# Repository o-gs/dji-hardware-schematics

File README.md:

# dji-hardware-schematics
Community made schematics for the DJI drones and devices.

The repository stored KiCad projects with schematocs and PCBs of various parts of DJI hardware.
These projects are community made, and very likely have errors. They come with no warranty.

If you see an error in a schematic, or want to contribute your own - you are free to do it. Your contribution will be verified and accepted into this repository.

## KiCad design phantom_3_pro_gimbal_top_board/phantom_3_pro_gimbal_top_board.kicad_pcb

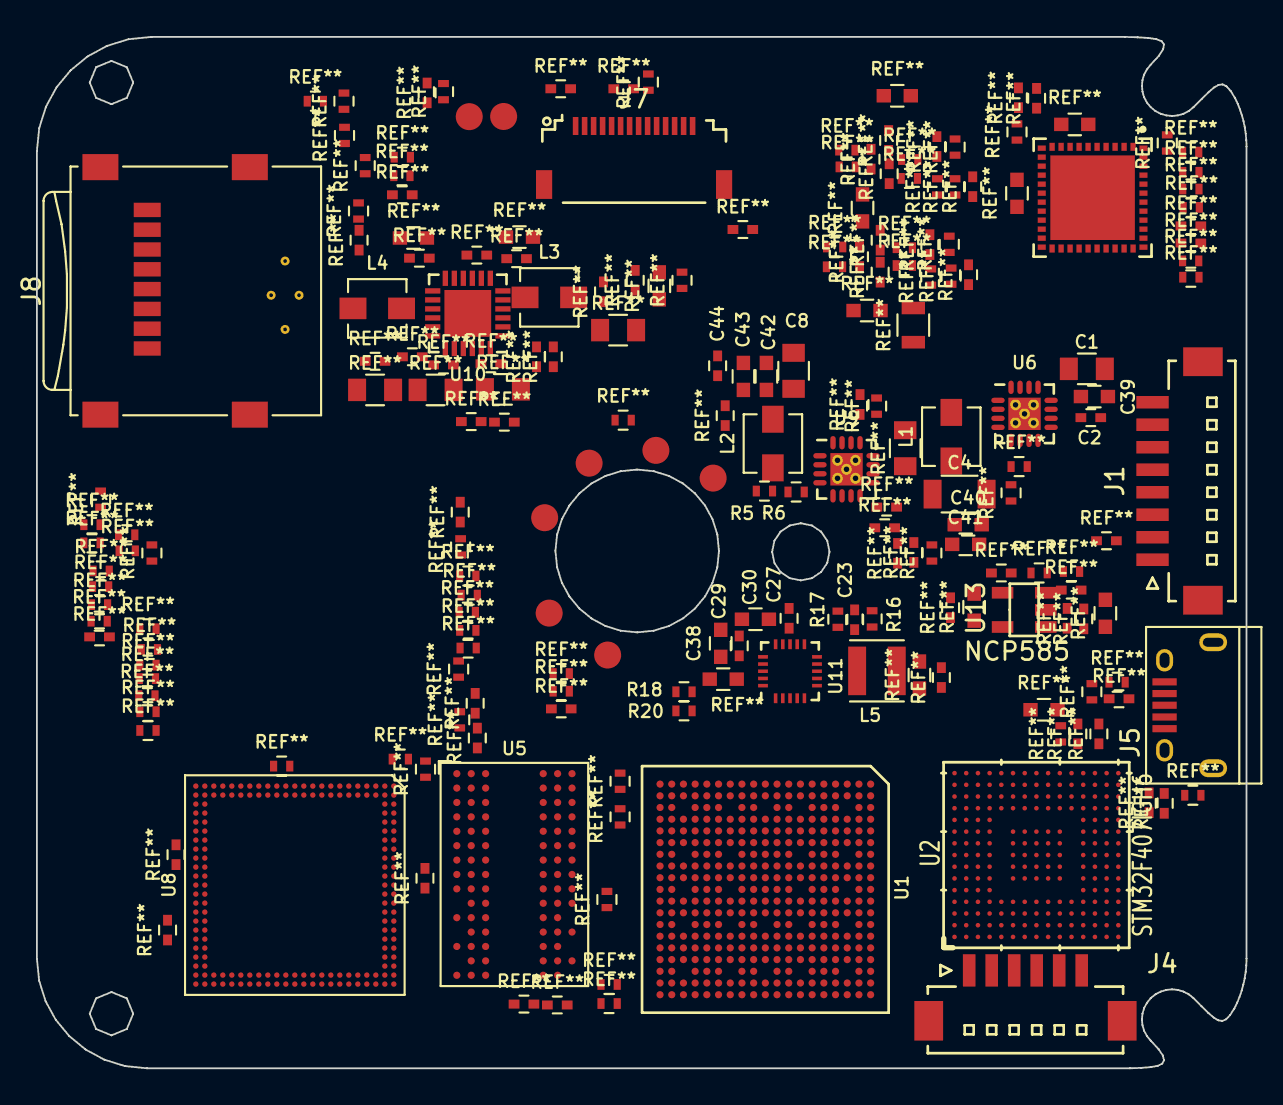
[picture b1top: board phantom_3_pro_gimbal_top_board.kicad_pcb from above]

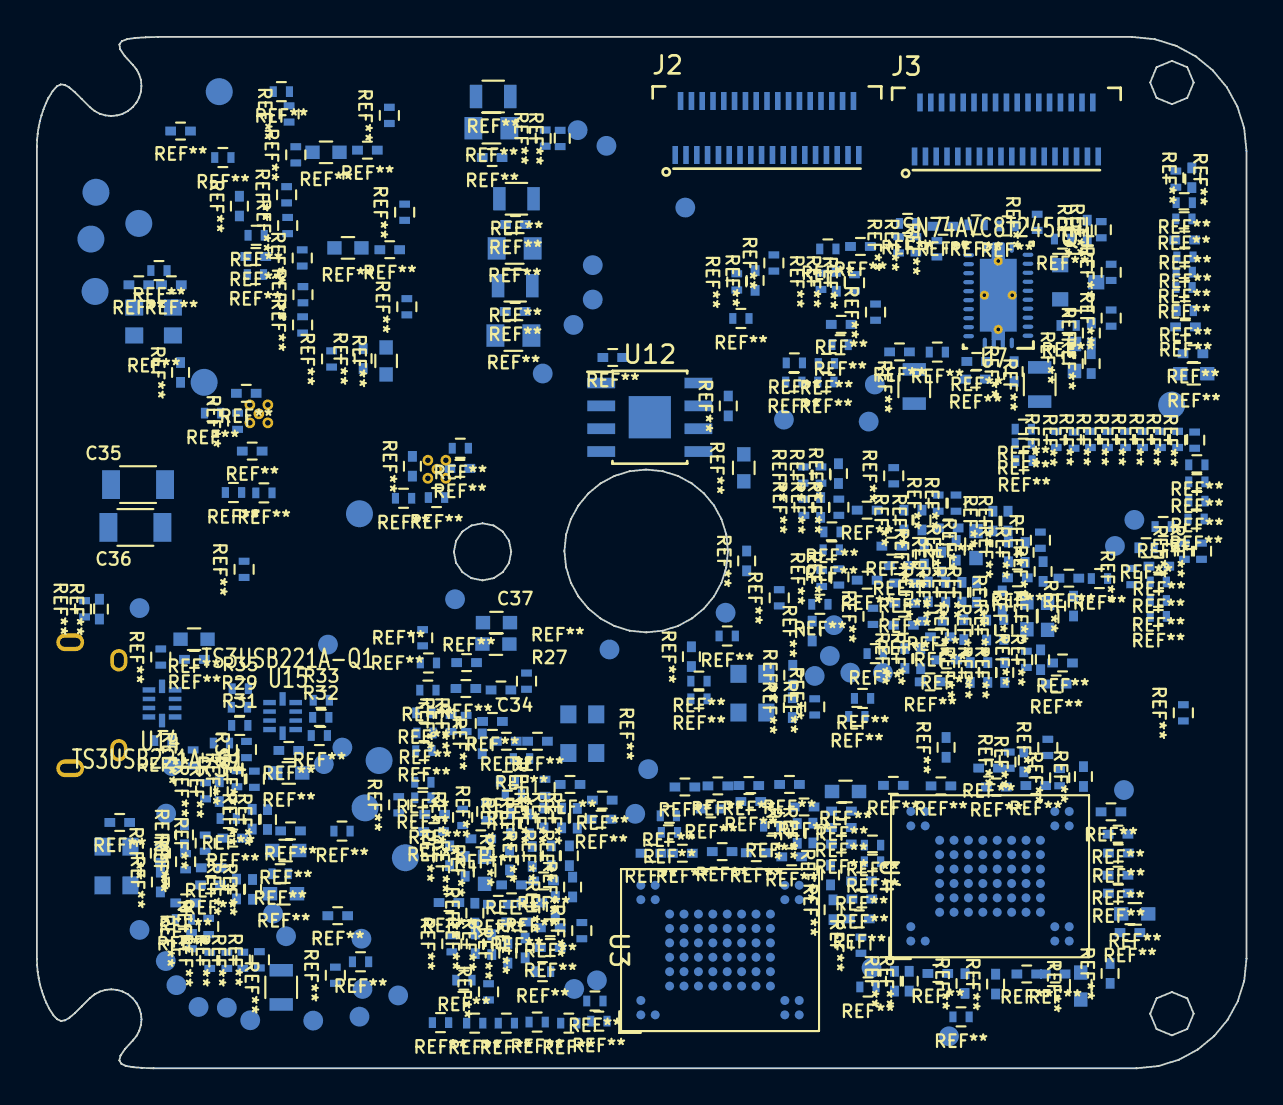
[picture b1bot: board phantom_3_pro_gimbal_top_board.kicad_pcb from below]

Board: 2 copper layers, 67.2 x 57.3 mm, 127 parts (78 on the bottom side), 45 nets, no tracks yet.

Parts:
C1: 10uF?; C_0805
C2: 100nF?; C_0402
C4: 2.2uF?; C_1206
C8: 2.2uF?; C_0805
C23: 22pF; C_0402
C27, C29: 10nF?; C_0402
C30, C37, C38: 2.2uF?; C_0603
C34: 1uF?; C_0402
C35, C36: 22uF?; C_1206
C39, C40, C42: 100nF?; C_0603
C41, C43: 10nF?; C_0603
C44: 100pF?; C_0402
J1: CONN_CENTER; Hirose_DF13C-08P-1.25V_08x1.25mm_Straight
J2: CONN_ARMS2; Flat_Foam_Conn-ZIF-35D-0.6H_35x0.60mm_Angled
J3: CONN_ARMS1; Flat_Foam_Conn-ZIF-35D-0.6H_35x0.60mm_Angled
J4: CONN_OFDM; Hirose_DF13C-06P-1.25V_06x1.25mm_Straight
J5: USB_OTG; USB_Micro-B
J7: CONN_MOTOR; Flat_Foam_Conn-14S-0.5H_14x0.50mm_Angled
J8: Micro_SD_Card; microSD_Card_Receptacle_Wuerth_693072010801
L1, L2, L3, L4: 2.2uH; L_Vishay_IHLP-1212
L5: 2.2uH; L_Neosid_SMS-ME3010
Q1: PMBT3904; SOT-23
R5, R6: 2.8kΩ?; R_0402
R16, R17: 220kΩ; R_0402
R18: 1kΩ; R_0402
R20: 50kΩ; R_0402
R27: 2kΩ; R_0402
R29, R31, R32, R33: 0Ω; R_0402
R34: ∞Ω; R_0402
R35, R36: 4.7kΩ; R_0402
TP1: CS_DSP; Measurement_Point_Round-SMD-Pad_Small
TP2: SCL_DSP; Measurement_Point_Round-SMD-Pad_Small
TP3: U0_R; Measurement_Point_Round-SMD-Pad_Small
TP4: U0_T; Measurement_Point_Round-SMD-Pad_Small
TP5: U3_CX; Measurement_Point_Round-SMD-Pad_Small
TP6: U3_RX; Measurement_Point_Round-SMD-Pad_Small
TP7: DM-; Measurement_Point_Round-SMD-Pad_Small
TP8: DP+; Measurement_Point_Round-SMD-Pad_Small
TP9: TMS; Measurement_Point_Round-SMD-Pad_Small
TP10: TDI; Measurement_Point_Round-SMD-Pad_Small
TP11: PGED; Measurement_Point_Round-SMD-Pad_Small
TP12: PGEC; Measurement_Point_Round-SMD-Pad_Small
TP13: SWCLK; Measurement_Point_Round-SMD-Pad_Small
TP14: TDO; Measurement_Point_Round-SMD-Pad_Small
TP15: MCLR_N; Measurement_Point_Round-SMD-Pad_Small
TP16: BOOT0; Measurement_Point_Round-SMD-Pad_Small
TP17: MOSI; Measurement_Point_Round-SMD-Pad_Small
TP18: SWDIO; Measurement_Point_Round-SMD-Pad_Small
TP19: RST; Measurement_Point_Round-SMD-Pad_Small
TP20: RSTEX; Measurement_Point_Round-SMD-Pad_Small
TP21: BT01; Measurement_Point_Round-SMD-Pad_Small
TP22: BT00; Measurement_Point_Round-SMD-Pad_Small
TP23: MC; Measurement_Point_Round-SMD-Pad_Small
TP24: B_S; Measurement_Point_Round-SMD-Pad_Small
TP25: 365; Measurement_Point_Round-SMD-Pad_Small
TP26: OUT6; Measurement_Point_Round-SMD-Pad_Small
TP27: OUT8; Measurement_Point_Round-SMD-Pad_Small
TP28: GIMBAL; Measurement_Point_Round-SMD-Pad_Small
TP29: CLK; Measurement_Point_Round-SMD-Pad_Small
TP30: U1_T1; Measurement_Point_Round-SMD-Pad_Small
TP31: U1_R1; Measurement_Point_Round-SMD-Pad_Small
TP32: 12V; Measurement_Point_Round-SMD-Pad_Small
TP33: +5V; Measurement_Point_Round-SMD-Pad_Small
TP34: CANH; Measurement_Point_Round-SMD-Pad_Small
TP35: CANL; Measurement_Point_Round-SMD-Pad_Small
TP36, TP39: 3.3VD; Measurement_Point_Round-SMD-Pad_Small
TP37: A9S_3.3VD; Measurement_Point_Round-SMD-Pad_Small
TP38: 3V3VD; Measurement_Point_Round-SMD-Pad_Small
TP40: VCC3V3; Measurement_Point_Round-SMD-Pad_Small
TP41: 1.8VD; Measurement_Point_Round-SMD-Pad_Small
TP42: VCC1V8; Measurement_Point_Round-SMD-Pad_Small
TP43: MB; Measurement_Point_Round-SMD-Pad_Small
TP44: MA; Measurement_Point_Round-SMD-Pad_Small
TP45: H2; Measurement_Point_Round-SMD-Pad_Small
TP46: H1; Measurement_Point_Round-SMD-Pad_Small
TP47: H3; Measurement_Point_Round-SMD-Pad_Small
TP48: U1RT; Measurement_Point_Round-SMD-Pad_Small
TP49: U1TT; Measurement_Point_Round-SMD-Pad_Small
TP50: URAT2_TX; Measurement_Point_Round-SMD-Pad_Small
TP51: URAT2_RX; Measurement_Point_Round-SMD-Pad_Small
TP52: VDDA; Measurement_Point_Round-SMD-Pad_Small
TP53: VDD; Measurement_Point_Round-SMD-Pad_Small
TP54: 1V2; Measurement_Point_Round-SMD-Pad_Small
TP55: 1.25DDR2; Measurement_Point_Round-SMD-Pad_Small
TP56, TP57, TP58, TP59, TP60, TP61, TP62, TP65: GND; Measurement_Point_Round-SMD-Pad_Small
TP63: 368_U0_RXP; Measurement_Point_Round-SMD-Pad_Small
TP64: 368_U0_TXP; Measurement_Point_Round-SMD-Pad_Small
U1: TMS320DM365ZCE; PBGA-N338_19x19_13x13mm_Pitch0.65mm
U2: STM32F407IGH6; UFBGA176p25-10x10mm_pitch0.65mm
U3: MT29F1G08; VFBGA-63_11x9_9.0x7.4mm_Pitch0.8mm
U4: MT29F2G08; VFBGA-63_11x9_9.0x7.4mm_Pitch0.8mm
U5: IS43DR16640B; BGA-84_2x3x15_8.0x12.5mm_Pitch0.8mm
U6, U9: TLV62130; QFN-16-1EP_3x3mm_Pitch0.5mm_ThermalVias
U7: SN74AVC8T245RHL; RHL0024_PVQFN-n24p4_4.3x6.3mm_Pitch0.5mm
U8: EDB8132B3PB; UFBGA-168_12x12mm_Pitch0.5mm
U10: LM26480; QFN-24-1EP_4x4mm_Pitch0.5mm
U11: TPS650061; QFN-20_3x3mm_Pitch0.4mm_NoMask
U12: MLX90316; SOIC-8-1EP_3.9x4.9mm_Pitch1.27mm
U13: NCP585; SOT-25
U14, U15: TS3USB221A-Q1; RSE10
U16: dsPIC33EP128MC504; VTLA-44_LGA-44_6x6mm_Pitch0.5mm

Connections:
/3.3VD: TP36.1, U14.10, U15.10
/EN_3.3: C34.1, R27.2, U11.3
/VCC1V2: C23.1, L5.2, R16.1, TP54.1, U1.E12, U1.G6, U1.G8, U1.H7, U1.H8, U1.H12, U1.J6, U1.J8, U1.J12, U1.J14, U1.K7, U1.K8, U1.K12, U1.M5
/VCC1V8: C29.1, C38.1, R27.1, TP42.1, U1.E5, U1.E9, U1.G9, U1.J7, U1.K6, U1.N9, U1.P7, U1.P9, U11.16, U11.17
/VCC3V3: C27.1, C37.1, R18.1, R20.1, TP40.1, U1.F6, U1.F7, U1.H6, U1.N6, U1.P4, U1.P5, U1.P6, U11.13, U11.14
/VDD1V1: C8.1, C42.1, C43.1, C44.1, L2.2, R5.1, TP53.1, U9.14
GND: C1.2, C2.2, C4.2, C8.2, C27.2, C29.2, C30.2, C34.2, C35.2, C36.2, C37.2, C38.2, C39.2, C40.2, C41.2, C42.2, C43.2, C44.2, J1.5, J1.6, J1.7, J1.8, J4.3, R6.2, R17.2, R35.1, R36.1, U1.D9, U1.F8, U1.F9, U1.H9, U1.J9, U1.J10, U1.J11, U1.K9, U1.L10, U1.L11, U1.N8, U1.P2, U1.P3, U1.W19, U6.6, U6.7, U6.8, U6.15, U6.16, U6.17, U9.6, U9.7, U9.8, U9.15, U9.16, U9.17, U10.2, U10.4, U10.9, U10.15, U10.18, U10.25, U11.6, U11.12, U11.21, U14.5, U15.5
unnamed: C23.2, R16.2, R17.1, U11.11
unnamed: R18.2, U11.19
unnamed: J4.1, R29.1
unnamed: J4.2, R31.1
unnamed: J4.4, R34.1
unnamed: J4.5, TP35.1
unnamed: J4.6, TP34.1
unnamed: J5.2, U14.4
unnamed: J5.3, U14.3
unnamed: J7.1, J7.2, J7.3
unnamed: J7.4, J7.5, J7.6
unnamed: J7.7, J7.8, J7.9
unnamed: L1.1, U6.1, U6.2, U6.3
unnamed: L2.1, U9.1, U9.2, U9.3
unnamed: L3.1, U10.5
unnamed: L4.1, U10.14
unnamed: L5.1, U11.7
unnamed: R5.2, R6.1, U9.5
unnamed: R20.2, U11.20
unnamed: R32.1, U15.3
unnamed: R29.2, U15.7
unnamed: R33.1, U15.4
unnamed: R31.2, U15.8
unnamed: R34.2, R36.2, U15.9
unnamed: R35.2, U15.6
unnamed: TP7.1, U15.2
unnamed: TP8.1, U15.1
unnamed: U3.G3, U3.G8
unnamed: U4.G3, U4.G8
unnamed: U5.A2, U5.E2, U5.R3, U5.R7, U5.R8
PVIN: C1.1, C2.1, C4.1, C30.1, C35.1, C36.1, C39.1, C40.1, C41.1, J1.1, J1.2, J1.3, J1.4, L1.2, TP32.1, TP33.1, U6.10, U6.11, U6.12, U6.13, U6.14, U9.10, U9.11, U9.12, U9.13, U11.8, U11.9, U11.15, U11.18
VCC: U3.D3, U3.G4, U3.H8, U3.J6, U4.D3, U4.G4, U4.H8, U4.J6
VDD: U5.A1, U5.E1, U5.J9, U5.M9, U5.R1
VDD1: U8.A11, U8.A20, U8.AB5, U8.AC20, U8.B3, U8.N2, U8.N22
VDD2: U8.AA2, U8.AB10, U8.AB21, U8.B11, U8.B21, U8.C2, U8.L22, U8.R2
VDDQ: U5.A9, U5.C1, U5.C3, U5.C7, U5.C9, U5.E9, U5.G1, U5.G3, U5.G7, U5.G9, U8.AA22, U8.AB13, U8.AB16, U8.AB19, U8.B13, U8.B16, U8.B19, U8.D22, U8.G22, U8.K22, U8.R22, U8.V22
VSS: U3.C5, U3.F7, U3.K3, U3.K8, U4.C5, U4.F7, U4.K3, U4.K8, U5.A3, U5.E3, U5.J3, U5.N1, U5.P9, U8.A12, U8.A15, U8.A18, U8.A21, U8.AA1, U8.AB7, U8.AB11, U8.AC5, U8.AC9, U8.AC12, U8.AC15, U8.AC18, U8.AC21, U8.B5, U8.B8, U8.B10, U8.C1, U8.C23, U8.F2, U8.F23, U8.J2, U8.J23, U8.M2, U8.M23, U8.P23, U8.R1, U8.U23, U8.V1, U8.Y23
VSSQ: U5.A7, U5.B2, U5.B8, U5.D2, U5.D8, U5.E7, U5.F2, U5.F8, U5.H2, U5.H8

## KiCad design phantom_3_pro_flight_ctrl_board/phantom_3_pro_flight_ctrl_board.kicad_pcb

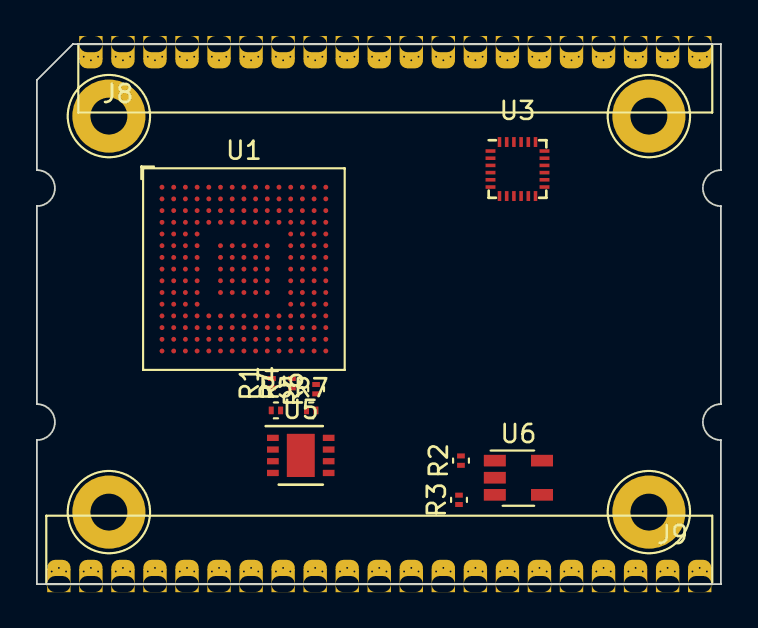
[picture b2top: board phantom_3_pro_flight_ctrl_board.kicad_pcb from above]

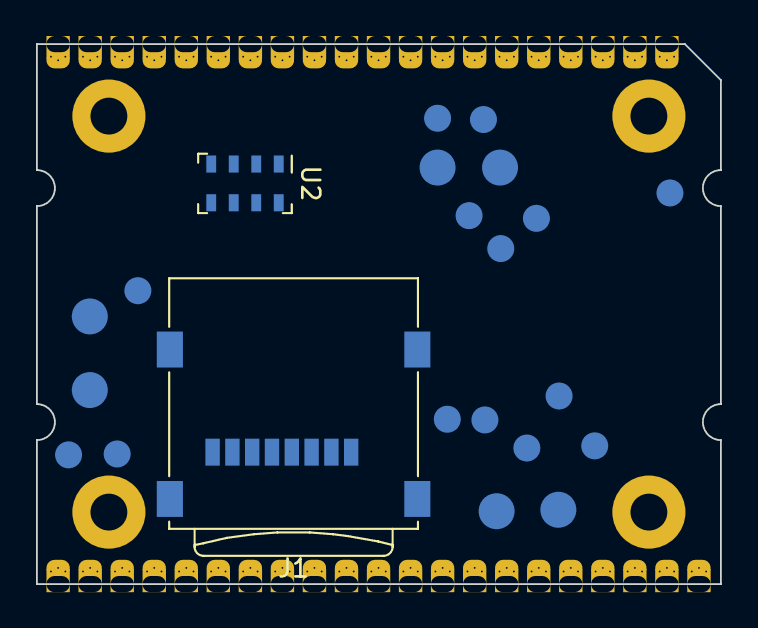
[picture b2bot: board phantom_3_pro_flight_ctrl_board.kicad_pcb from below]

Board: 2 copper layers, 38.0 x 30.0 mm, 35 parts (22 on the bottom side), 12 nets, no tracks yet.

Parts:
J1: Micro_SD_Card; microSD_Card_Receptacle_Wuerth_693072010801
J8: CONN_MC_FRONT; Connector-edge-20pin-1.78mm-cut
J9: CONN_MC_BACK; Connector-edge-21pin-1.78mm-cut
R1, R4: 22Ω; R_0201
R2, R5, R7: 10kΩ; R_0201
R3: 15,7kΩ; R_0201
R6: 100Ω; R_0201
TP1: U3_RX; Measurement_Point_Round-SMD-Pad_Small
TP2: U3_TX; Measurement_Point_Round-SMD-Pad_Small
TP3: BOOT0; Measurement_Point_Round-SMD-Pad_Small
TP4, TP16: GND; Measurement_Point_Round-SMD-Pad_Big
TP5: 5V; Measurement_Point_Round-SMD-Pad_Big
TP6: VCC3V6; Measurement_Point_Round-SMD-Pad_Small
TP7: U7_RX; Measurement_Point_Round-SMD-Pad_Small
TP8: U7_TX; Measurement_Point_Round-SMD-Pad_Small
TP9: CAN1_T; Measurement_Point_Round-SMD-Pad_Big
TP10: SWDIO; Measurement_Point_Round-SMD-Pad_Small
TP11: CAN1_R; Measurement_Point_Round-SMD-Pad_Big
TP12: PB11; Measurement_Point_Round-SMD-Pad_Small
TP13: VCC3V3; Measurement_Point_Round-SMD-Pad_Big
TP14: PB10; Measurement_Point_Round-SMD-Pad_Small
TP15: SWCLK; Measurement_Point_Round-SMD-Pad_Small
TP17, TP18: GND; Measurement_Point_Round-SMD-Pad_Small
TP19: DAC_OUT; Measurement_Point_Round-SMD-Pad_Small
TP20: 3V3A; Measurement_Point_Round-SMD-Pad_Small
U1: STM32F427II; BGA-176p25_10x10_11.0x11.0mm_Pitch0.65mm
U2: MS5607; LGA-8_3x5mm_Pitch1.25mm
U3: MPU-6500; QFN-24_3x3mm_Pitch0.4mm
U5: PA 5xA; DFN-8-1EP_3x3mm_Pitch0.65mm
U6: RC09; TSOT-23-5

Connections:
/3V3A: TP20.1, U6.5
/3V6: J9.10, R2.2, TP6.1, U5.8, U6.1
/5V: J9.14, TP5.1
/U3_RX: J8.7, TP1.1
/U3_TX: J8.8, TP2.1
/U7_RX: J9.3, TP7.1
/U7_TX: J9.2, TP8.1
/VCC3V3: J1.4, R5.1, R7.2, TP13.1, U1.C5, U1.C7, U1.C8, U1.C9, U1.F3, U1.G3, U1.G13, U1.H13, U1.J12, U1.J13, U1.K4, U1.N8, U1.N9, U1.N10, U5.1
GND: J1.6, J8.2, J8.6, J8.9, J8.11, J8.15, J8.18, J9.4, J9.6, J9.11, J9.18, J9.21, R3.1, TP4.1, U1.D5, U1.D7, U1.D8, U1.D9, U1.F2, U1.F6, U1.F7, U1.F8, U1.F9, U1.F10, U1.F12, U1.G2, U1.G6, U1.G7, U1.G8, U1.G9, U1.G10, U1.G12, U1.H6, U1.H7, U1.H8, U1.H9, U1.H10, U1.H12, U1.J6, U1.J7, U1.J8, U1.J9, U1.J10, U1.K6, U1.K7, U1.K8, U1.K9, U1.K10, U1.M8, U1.M9, U2.3, U3.18, U3.20, U5.4, U6.2
unnamed: R2.1, R3.2, U6.3
unnamed: R5.2, R6.2
unnamed: TP3.1, U1.D6

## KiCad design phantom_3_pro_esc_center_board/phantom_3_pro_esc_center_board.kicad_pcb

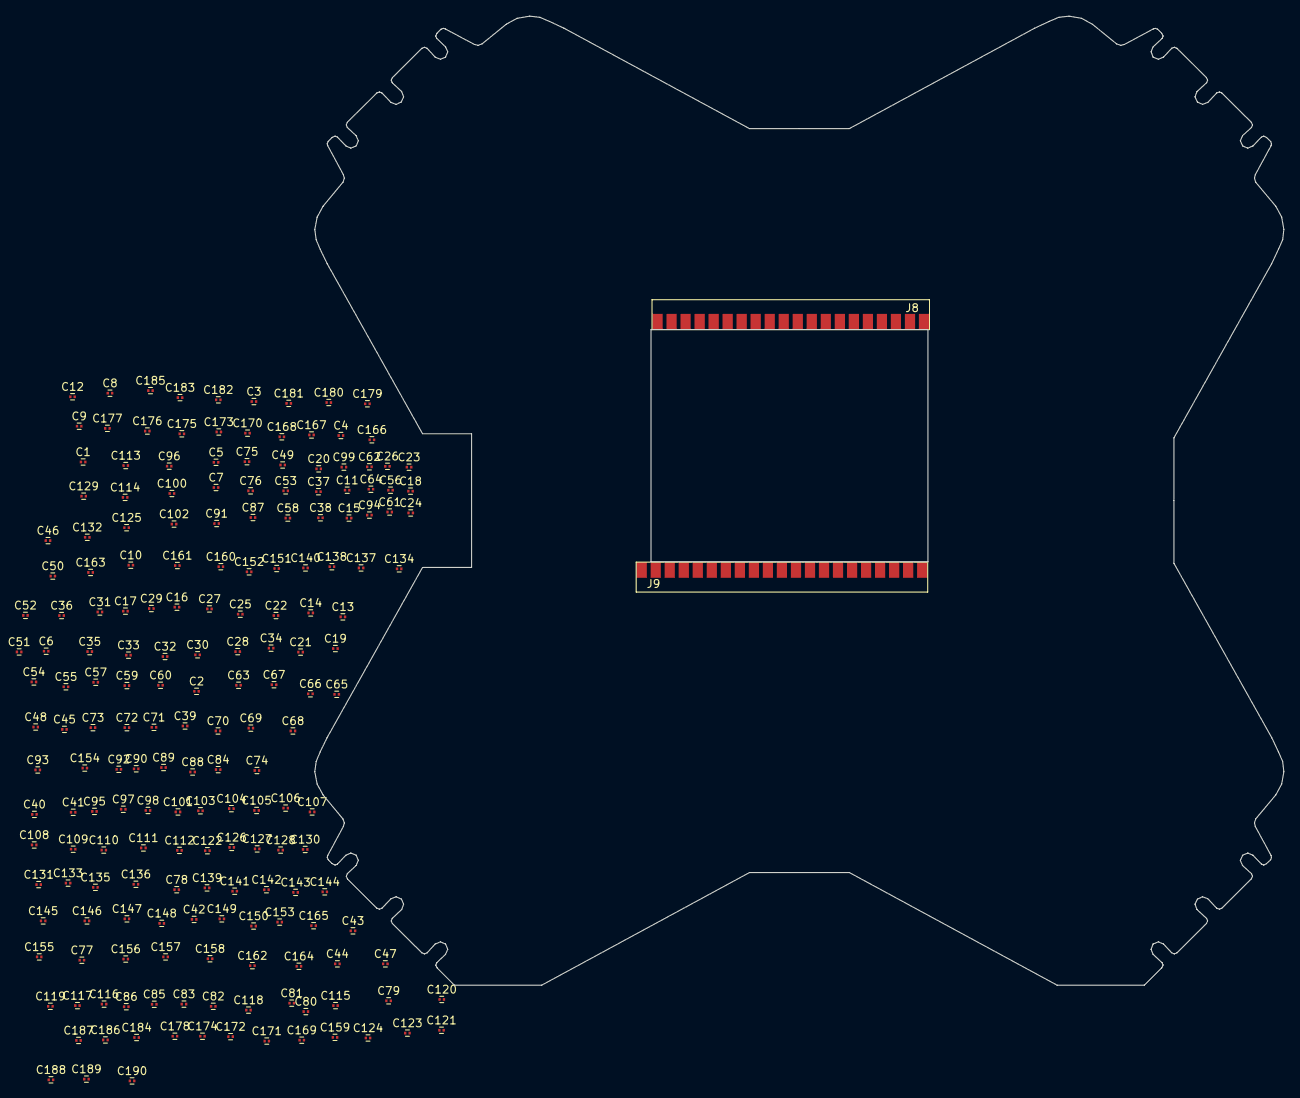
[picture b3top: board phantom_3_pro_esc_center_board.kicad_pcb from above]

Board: 2 copper layers, 123.0 x 123.0 mm, 192 parts (0 on the bottom side), 14 nets, no tracks yet.

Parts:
C1, C4, C5, C6, C9, C10, C39, C42, C43, C44, C47, C48, C77, C80, C81, C82, C85, C86, C115, C118, C119, C120, C123, C124, C172: 100nF; C_0201
C2, C3, C40, C41, C78, C79, C116, C117: 220uF; C_0201
C7, C45, C83, C121: 120pF; C_0201
C8, C46, C84, C122: 6,8nF; C_0201
C11, C49, C87, C125: 15nF; C_0201
C12, C29, C50, C67, C88, C105, C126, C143, C153, C154, C156, C157: 4,7uF; C_0201
C13, C14, C16, C19, C22, C30, C51, C52, C54, C57, C60, C68, C89, C90, C92, C95, C98, C106, C127, C128, C130, C133, C136, C144: 0,1uF; C_0201
C15, C53, C91, C129, C175, C176, C179, C180: 47uF; C_0201
C17, C21, C25, C31, C32, C33, C34, C35, C36, C55, C59, C63, C69, C70, C71, C72, C73, C74, C93, C97, C101, C107, C108, C109, C110, C111, C112, C131, C135, C139, C145, C146, C147, C148, C149, C150, C155, C158, C162, C164: 2,2uF; C_0201
C18, C23, C56, C61, C94, C99, C132, C137: 1nF; C_0201
C20, C58, C96, C134: 22nF; C_0201
C24, C26, C62, C64, C100, C102, C138, C140, C168, C170, C183: 1uF; C_0201
C27, C28, C65, C66, C103, C104, C141, C142: 2,2nF; C_0201
C37, C38, C75, C76, C113, C114, C151, C152: 36pF; C_0201
C159: 270pF; C_0201
C160, C161, C163, C166, C167, C173, C177: 10nF; C_0201
C165: 3,3nF; C_0201
C169: 100pF; C_0201
C171: 100nF?; C_0201
C174: 2,2nF?; C_0201
C178: 22pF?; C_0201
C181: 8uF; C_0201
C182: 28uF; C_0201
C184: 220pF; C_0201
C185: ?pF; C_0201
C186, C187, C188, C189, C190: 100uF; C_0201
J8: CONN_MC_FRONT; Connector-edge-20pin-1.78mm
J9: CONN_MC_BACK; Connector-edge-21pin-1.78mm

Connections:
+3V3: C32.1, C70.1, C108.1, C146.1
+BATT: C2.1, C3.1, C4.1, C5.1, C12.2, C13.2, C21.2, C25.2, C29.1, C30.1, C31.2, C40.1, C41.1, C42.1, C43.1, C50.2, C51.2, C59.2, C63.2, C67.1, C68.1, C69.2, C78.1, C79.1, C80.1, C81.1, C88.2, C89.2, C97.2, C101.2, C105.1, C106.1, C107.2, C116.1, C117.1, C118.1, C119.1, C126.2, C127.2, C135.2, C139.2, C143.1, C144.1, C145.2, C153.2, C154.2, C155.2, C156.2, C157.2, C158.2, C160.2, C161.2, C162.2, C164.2, C168.2, C170.2, J9.12
/3V6: C175.2, C179.2, C181.2, J9.10
/5V: C176.2, C180.2, C182.2, J9.14
/12V: C186.2, C187.2, C188.2, C189.2, C190.2
GND: C1.2, C2.2, C3.2, C4.2, C6.2, C7.1, C9.2, C10.2, C11.1, C12.1, C13.1, C15.2, C17.2, C18.2, C21.1, C23.2, C24.2, C25.1, C26.2, C27.1, C28.1, C29.2, C30.2, C31.1, C32.2, C33.2, C34.2, C35.2, C36.2, C37.2, C38.2, C39.2, C40.2, C41.2, C42.2, C44.2, C45.1, C47.2, C48.2, C49.1, C50.1, C51.1, C53.2, C55.2, C56.2, C59.1, C61.2, C62.2, C63.1, C64.2, C65.1, C66.1, C67.2, C68.2, C69.1, C70.2, C71.2, C72.2, C73.2, C74.2, C75.2, C76.2, C77.2, C78.2, C79.2, C80.2, C82.2, C83.1, C85.2, C86.2, C87.1, C88.1, C89.1, C91.2, C93.2, C94.2, C97.1, C99.2, C100.2, C101.1, C102.2, C103.1, C104.1, C105.2, C106.2, C107.1, C108.2, C109.2, C110.2, C111.2, C112.2, C113.2, C114.2, C115.2, C116.2, C117.2, C118.2, C120.2, C121.1, C123.2, C124.2, C125.1, C126.1, C127.1, C129.2, C131.2, C132.2, C135.1, C137.2, C138.2, C139.1, C140.2, C141.1, C142.1, C143.2, C144.2, C145.1, C146.2, C147.2, C148.2, C149.2, C150.2, C151.2, C152.2, C153.1, C154.1, C155.1, C156.1, C157.1, C158.1, C159.1, C160.1, C161.1, C162.1, C163.1, C164.1, C166.1, C167.1, C168.1, C170.1, C175.1, C176.1, C177.1, C178.1, C179.1, C180.1, C181.1, C182.1, C184.1, C185.1, C186.1, C187.1, C188.1, C189.1, C190.1, J8.2, J8.6, J8.9, J8.11, J8.15, J8.18, J9.4, J9.6, J9.11, J9.13, J9.18, J9.21
unnamed: C7.2, C8.2
unnamed: C45.2, C46.2
unnamed: C83.2, C84.2
unnamed: C121.2, C122.2
unnamed: C165.1, C169.1
unnamed: C173.2, C177.2
unnamed: C174.2, C178.2
VCC: C15.1, C53.1, C91.1, C129.1

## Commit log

2017-04-24 First version of ESC schematic.
2017-04-25 Added PDF schematic.
2017-04-26 Renumbered components.
2017-07-17 Added drone overview schematic.
    Overview will store simplified, high-level schematics.
2017-07-17 GIT config update to ignore backups.
2017-07-17 Overview: LED board update.
2017-07-17 Added back components to ESC center board PCB.
2017-07-19 Overview: Conceptual schematics of some components.
2017-07-20 Overview: Added OFDM board.
    Besides drawing the OFDM, components were updated.
2017-07-25 Overview: Work on camera and gimbal.
2017-07-25 ESC Center: Identified pins of FC connection.
    Named all FC pins, and linked with proper connectors.
2017-07-25 ESC Center: Added ESC connection to FC.
    The ESC-FC connection is made through resistors,
    so I haven't identified it in first check.
2017-07-25 Overview: Updated LED board to match reality.
2017-07-28 ESC Center: Updated to latest findings.
2017-07-28 Flight Ctrl: Started work on the board.
2017-07-28 Overview: Updated gimbal control board.
2017-07-29 ESC Center: Added schematics of switching converters.
2017-07-29 Overview: Added power converters.
2017-07-29 Overview: Drawn the camera encoder block.
2017-07-29 Overview: Updated PDF export.
2017-07-29 ESC Center: Updated PDF export.
2017-07-30 Overview: Started work on camera sensor brd.
2017-08-03 Flight Ctrl: drawn DC conv and better uC schematic.
    DC-DC converters have now some of surroundings mapped.
    Also, the main uC schematic was divided into 4 parts
    and properly defined.
2017-08-03 Overview: Updated VPS definition.
    Placed proper components into VPS schematics.
    No connections are made between components yet.
2017-08-03 Updated PDF exports.
    The schematics exported to PDF were updated.
2017-08-08 Flight Ctrl: Started work on PCB.
    WIP on edge connectors.
2017-08-11 Flight Ctrl: Updated uC component to map to BGA.
    The microcontroller model was updated so that pin numbers map
    to numbers in BGA footprint.
    Also, edge pad connector footprints were updated.
2017-08-11 ESC Center: Formed a link between schematic and PCB.
    Modified PCB to link some components to schematic.
    Also created edge pad connectors to FC board.
2017-08-12 Flight Ctrl: Added SD card and IMU.
    The IMU is placed on separate board, but there are
    footprints on the flight controller PCB to solder
    it directly as well.
2017-08-12 Flight Ctrl: Updated PDF.
    Just plotted the current project.
2017-10-01 Gimbal Top: Added the project.
    It has basic PCB layout already prepared, and a few symbols created
    for schematics.
2017-10-07 Gimbal Top: Better symbols, dc-dc circuits
    Symbols were updated so that pins match to footpints.
    More footprints added.
    Switching regulator circuits were drawn based on application examples.
2017-10-07 Gimbal Top: Created PDF.
    Updated page size to fit schematics, and exported to PDF.
2017-10-08 Gimbal Top: Measured and filled part of DC-DC conv
    Checked part of voltage regulator circuits with multimeter.
    Associated a few footprints with schematic, updated values.
2017-10-09 Gimbal Top: updated PDFs.
2017-10-15 Gimbal Top: Added more symbols and footprints.
2017-10-15 Flight Ctrl: Just renamed a symbol library, no real change.
2017-10-15 Overview: Updated to latest findings.
    Added magnetometer to gimbal control, and made some minor fixes.
2017-10-16 Gimbal Top: Update PDFs.
2017-11-28 Overview: Separated gimbal power circuit.
    This is to make sure the connection won't be interpreted as data link.
2017-12-05 Overview: Updated encoder to include micro-USB.
2017-12-05 Gimbal Top: Drawn USB circuits, and USB mux'es.
    USB multiplexers are used for both USB outputs, though
    connected in very different ways.
2019-01-16 Gimbal/ESC Center: Minor updates.
2019-01-16 All: Preparing for KiCad version change.
2019-01-16 ESC Center: Upgraded to KiCAD 5.0.1.
2019-01-16 Flight Ctrl: Upgraded to KiCAD 5.0.1.
2019-01-16 Overview: Upgraded to KiCAD 5.0.1.
2019-01-17 All: Finished updating to KiCad 5.0.1.
2019-01-22 Mavic: Gimbal Control Board.
2020-08-30 mav mini: Added ESC Power Board diagnostic voltages
    Drone de Garagem shared the voltages.
2021-05-08 mav mini: 2nd ESC Power Board diagnostic voltages
    This one shared by Jeff Drones.
